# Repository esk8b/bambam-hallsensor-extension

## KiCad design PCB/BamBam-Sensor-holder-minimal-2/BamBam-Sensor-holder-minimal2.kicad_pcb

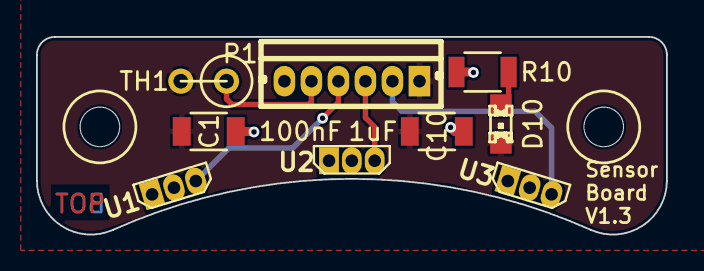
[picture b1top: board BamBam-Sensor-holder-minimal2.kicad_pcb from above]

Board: 2 copper layers, 35.0 x 11.0 mm, 11 parts (0 on the bottom side), 7 nets.

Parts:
C1: 100nF; C_1206
C10: 1uF; C_1206
D10: blau; LED-0805
H1, H2: 2mm; MountingHole_2mm
P1: CONN_01X06; B6B-ZR
R10: 220; R_1206
TH1: THERMISTOR; R1
U1, U2, U3: DRV5013AD; P-SSO-3-2

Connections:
/A: P1.4, U1.3
/B: P1.3, U2.3
/C: P1.2, U3.3
/Temp: P1.5, TH1.1
/Vcc: C1.1, C10.1, P1.6, R10.1, U1.1, U2.1, U3.1
GND: C1.2, C10.2, D10.2, P1.1, TH1.2, U1.2, U2.2, U3.2
unnamed: D10.1, R10.2

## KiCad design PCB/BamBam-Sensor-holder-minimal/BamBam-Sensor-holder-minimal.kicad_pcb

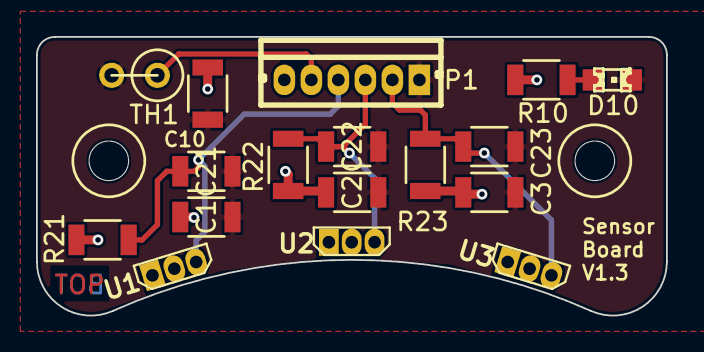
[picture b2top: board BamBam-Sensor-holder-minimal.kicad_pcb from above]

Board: 2 copper layers, 35.0 x 15.5 mm, 19 parts (0 on the bottom side), 7 nets.

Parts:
C1, C2, C3: 100nF; R_1206
C10: 1uF; R_1206
C21, C22, C23: 680pF; R_1206
D10: blau; LED-0805
H1: 3mm; MountingHole_3mm
H2: 3mm; MountingHole_2mm
P1: CONN_01X06; B6B-ZR
R10: 220; R_1206
R21, R22, R23: 10k; R_1206
TH1: THERMISTOR; R1
U1, U2, U3: DRV5013AD; P-SSO-3-2

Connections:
/A: C21.1, P1.4, R21.2, U1.3
/B: C22.1, P1.3, R22.2, U2.3
/C: C23.1, P1.2, R23.2, U3.3
/Temp: P1.5, TH1.1
/Vcc: C1.1, C2.1, C3.1, C10.1, P1.6, R10.1, R21.1, R22.1, R23.1, U1.1, U2.1, U3.1
GND: C1.2, C2.2, C3.2, C10.2, C21.2, C22.2, C23.2, D10.2, P1.1, TH1.2, U1.2, U2.2, U3.2
unnamed: D10.1, R10.2

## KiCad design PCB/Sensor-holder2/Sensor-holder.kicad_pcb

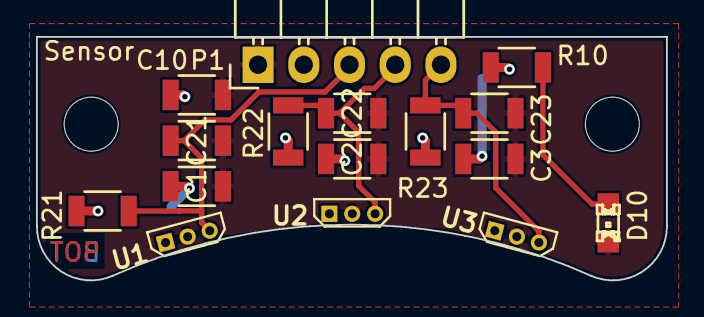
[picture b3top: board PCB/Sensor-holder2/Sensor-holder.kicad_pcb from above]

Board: 2 copper layers, 35.0 x 13.5 mm, 18 parts (0 on the bottom side), 6 nets.

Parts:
C1, C2, C3: 100nF; R_1206
C10: 1uF; R_1206
C21, C22, C23: 680pF; R_1206
D10: blau; LED-0805
H1, H2: 3mm; MountingHole_3mm
P1: CONN_01X05; Pin_Header_Angled_1x05
R10: 470; R_1206
R21, R22, R23: 10k; R_1206
U1, U2, U3: DRV5013AD; P-SSO-3-2

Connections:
/A: C21.1, P1.3, R21.2, U1.3
/B: C22.1, P1.4, R22.2, U2.3
/C: C23.1, P1.5, R23.2, U3.3
/Vcc: C1.1, C2.1, C3.1, C10.1, P1.2, R10.1, R21.1, R22.1, R23.1, U1.1, U2.1, U3.1
GND: C1.2, C2.2, C3.2, C10.2, C21.2, C22.2, C23.2, D10.2, P1.1, U1.2, U2.2, U3.2
unnamed: D10.1, R10.2

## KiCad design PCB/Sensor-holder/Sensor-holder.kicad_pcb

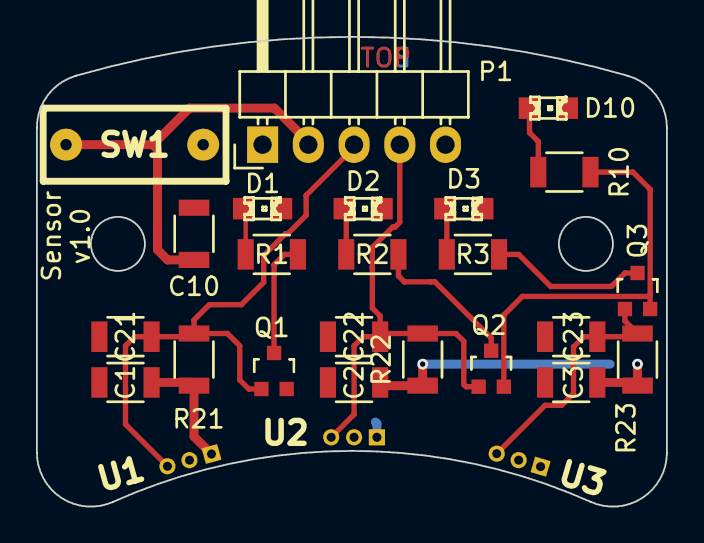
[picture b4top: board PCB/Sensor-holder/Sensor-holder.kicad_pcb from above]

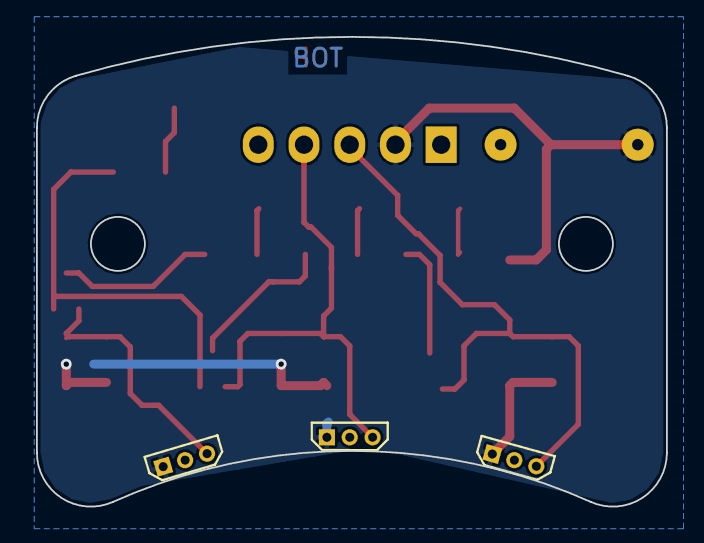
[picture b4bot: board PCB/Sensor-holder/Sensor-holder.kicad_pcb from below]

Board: 2 copper layers, 35.0 x 26.1 mm, 26 parts (3 on the bottom side), 13 nets.

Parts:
C1, C2, C3: 100nF; R_1206
C10: 1uF; R_1206
C21, C22, C23: 680pF; R_1206
D1: grün; LED-0805
D2: gelb; LED-0805
D3: rot; LED-0805
D10: blau; LED-0805
P1: CONN_01X05; Pin_Header_Angled_1x05
Q1, Q2, Q3: IRLML6402; PMOSFET_SOT23
R1, R2, R3, R10: 470; R_1206
R21, R22, R23: 10k; R_1206
SW1: LED; DIPS-DS01
U1, U2, U3: DRV5013AD; P-SSO-3-2

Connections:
/A: C21.1, P1.3, Q1.G, R21.2, U1.3
/B: C22.1, P1.4, Q2.G, R22.2, U2.3
/C: C23.1, P1.5, Q3.G, R23.2, U3.3
/Vcc: C1.1, C2.1, C3.1, C10.1, P1.2, R21.1, R22.1, R23.1, SW1.2, U1.1, U2.1, U3.1
GND: C1.2, C2.2, C3.2, C10.2, C21.2, C22.2, C23.2, D1.2, D2.2, D3.2, D10.2, P1.1, U1.2, U2.2, U3.2
unnamed: D1.1, R1.2
unnamed: D2.1, R2.2
unnamed: D3.1, R3.2
unnamed: D10.1, R10.2
unnamed: Q1.D, R1.1
unnamed: Q1.S, Q2.S, Q3.S, R10.1, SW1.1
unnamed: Q2.D, R2.1
unnamed: Q3.D, R3.1

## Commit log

2015-03-22 Erster Entwurf der Hall Sensor Platine
2015-03-22 Design Regeln für die Leiterbahnen und Vias definiert. Einstellungen aus dem Teensy Projekt.
2015-03-23 Dip Switch eingearbeitet. Layout wird dadurch suboptimal.
2015-03-24 Sensor Holder 2 ohne LEDs. Schaltplan und Hall-Bauelemente müssten Korrektur gelesen werden.
2015-03-26 Der BamBam-Sensor-Holder-Minimal hat jetzt seinen richtigen Namen gekommen. Es wurde eine JST-ZH Buchse nach den Vorgaben von ROAR RULES 2010 verwendet. Ein Temperatursensor gemäß ROAR RULES 2010 kan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
2015-03-27 Hallsensor Acschluss Pin Belegung JST ZHR6 hinzugefuegt
2015-03-27 So wurden die Daten in Auftrag gegeben
2015-03-28 Den Pfadnamen angepasst
2015-04-09 Bohrungen Mount auf 3.2mm vergrößert Bohrungen Hall-Sensoren von 0.5mm auf 0.7mm vergrößert. Versionsnummer angepasst LED-Widerstand angepasst
2015-04-10 zusammenführen
2015-04-16 Anpassung an KiCad > 02/2015 Kleine Korrekturen des Layouts Sensoren um 0.6° weiter auseinander gestellt.
2015-04-28 Sensoren Pads vergrößert Winkel der Sensorenanordnung überprüft und angepasst.
2015-05-02 Die Sensoren sind von der Leiterplattenkante 0.254mm entfernt. Der Anschlussstecker wurde am Mittelsensor ausgerichtet. Die Versionsnummer wurde auf 1.3 angehoben. Layout optimiert, bessere GND-Verso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
2015-05-11 Es wurde eine reduzierte Version der Hall-Sensoren Platine mit der Bezeichnung BamBam Sensor Holder minimal 2 erstellt und in Produktion gegeben. Die Sensoren sind jetzt exakt auf 63mm Motoren mit 17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
2015-05-24 Libs manuell eingebunden
2015-10-11 Aktuelle Sensorhalter von eXo als STL-Datei. Datum 05.10.2015
